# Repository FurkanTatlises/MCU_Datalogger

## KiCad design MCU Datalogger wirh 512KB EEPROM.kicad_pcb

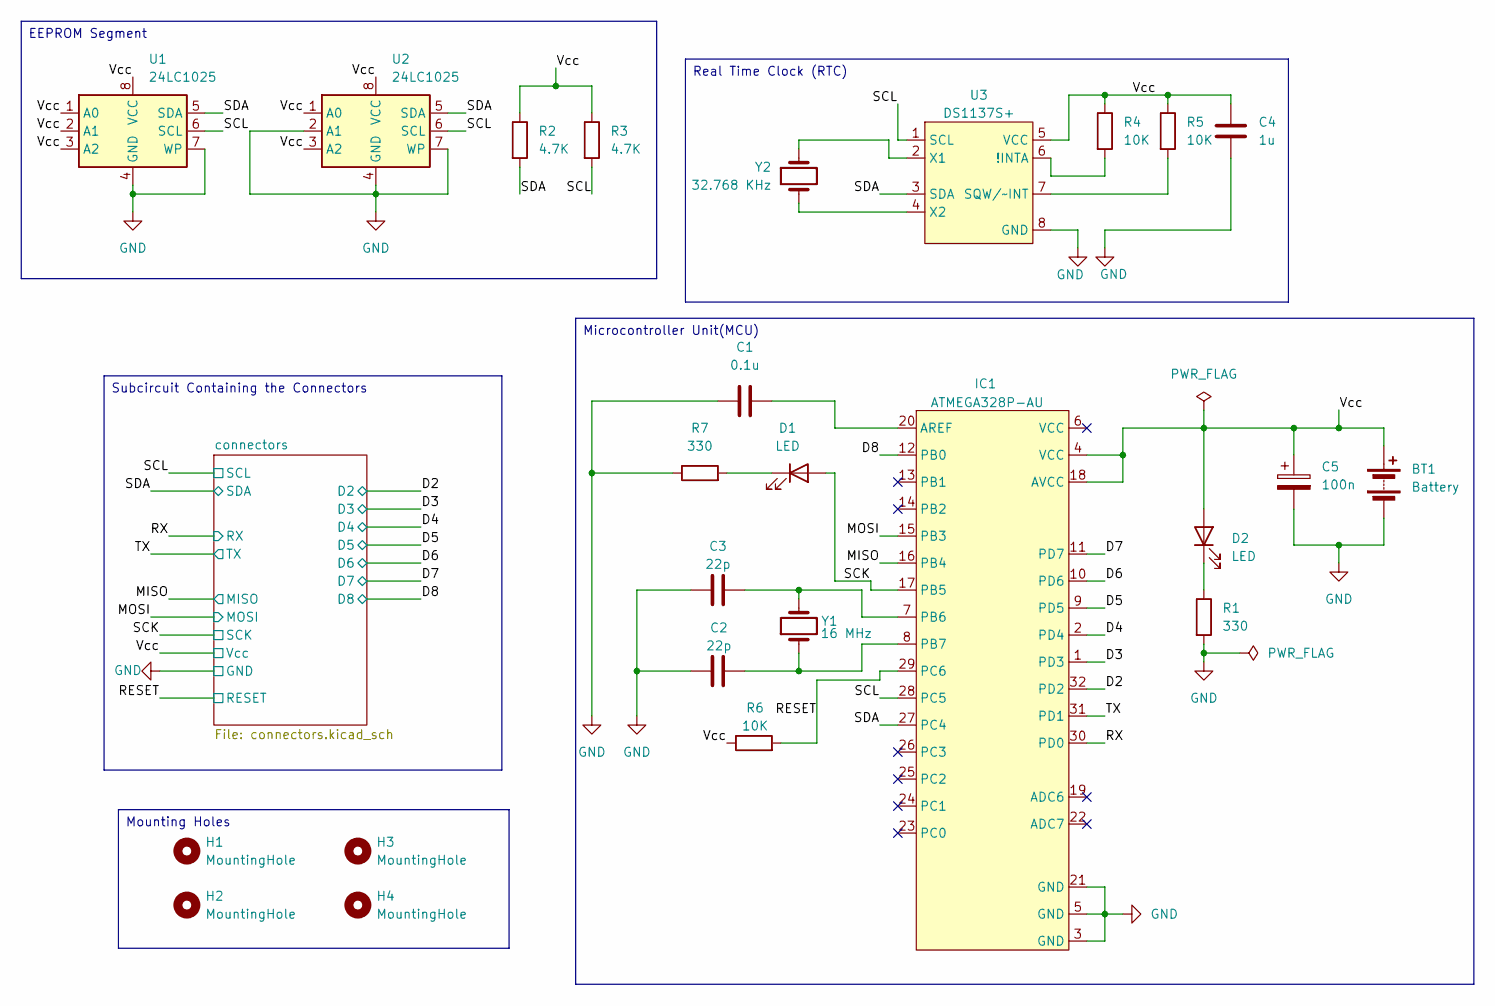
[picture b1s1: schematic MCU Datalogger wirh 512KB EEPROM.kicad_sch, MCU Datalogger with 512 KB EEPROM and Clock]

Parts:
BT1: Battery; PinHeader_1x02_P2.54mm_Vertical
C1: 0.1u; C_1206_3216Metric
C2, C3: 22p; C_1206_3216Metric
C4: 1u; C_1206_3216Metric
C5: 100n; C_1206_3216Metric
D1, D2: LED; LED_1206_3216Metric
H1, H2, H3, H4: MountingHole; MountingHole_2.1mm
IC1: ATMEGA328P-AU
R1, R7: 330; R_0805_2012Metric
R2, R3: 4.7K; R_0805_2012Metric
R4, R5, R6: 10K; R_0805_2012Metric
U1, U2: 24LC1025; SOIC-8_5.3x5.3mm_P1.27mm
U3: DS1137S+; DS1337S+
Y1: 16 MHz; Crystal_SMD_5032-2Pin_5.0x3.2mm
Y2: 32.768 KHz; Crystal_SMD_5032-2Pin_5.0x3.2mm

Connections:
/D2: IC1.32 (PD2); also elsewhere on the board
/D3: IC1.1 (PD3); also elsewhere on the board
/D4: IC1.2 (PD4); also elsewhere on the board
/D5: IC1.9 (PD5); also elsewhere on the board
/D6: IC1.10 (PD6); also elsewhere on the board
/D7: IC1.11 (PD7); also elsewhere on the board
/D8: IC1.12 (PB0); also elsewhere on the board
/MISO: IC1.16 (PB4); also elsewhere on the board
/MOSI: IC1.15 (PB3); also elsewhere on the board
/RESET: IC1.29 (PC6), R6.2; also elsewhere on the board
/RX: IC1.30 (PD0); also elsewhere on the board
/SCK: D1.2 (A), IC1.17 (PB5); also elsewhere on the board
/SCL: IC1.28 (PC5), R3.2, U1.6 (SCL), U2.6 (SCL), U3.1 (SCL); also elsewhere on the board
/SDA: IC1.27 (PC4), R2.2, U1.5 (SDA), U2.5 (SDA), U3.3 (SDA); also elsewhere on the board
/TX: IC1.31 (PD1); also elsewhere on the board
/Vcc: BT1.1 (+), C4.2, C5.1, D2.2 (A), IC1.4 (VCC), IC1.18 (AVCC), R2.1, R3.1, R4.1, R5.1, R6.1, U1.1 (A0), U1.2 (A1), U1.3 (A2), U1.8 (VCC), U2.1 (A0), U2.3 (A2), U2.8 (VCC), U3.5 (VCC); also elsewhere on the board
GND: BT1.2 (-), C1.2, C2.1, C3.1, C4.1, C5.2, IC1.3 (GND), IC1.5 (GND), IC1.21 (GND), R1.2, R7.1, U1.4 (GND), U1.7 (WP), U2.2 (A1), U2.4 (GND), U2.7 (WP), U3.8 (GND); also elsewhere on the board
unnamed: D1.1 (K), R7.2
unnamed: D2.1 (K), R1.1
unnamed: C1.1, IC1.20 (AREF)
unnamed: C3.2, IC1.7 (PB6), Y1.2
unnamed: C2.2, IC1.8 (PB7), Y1.1
unnamed: R4.2, U3.6 (!INTA)
unnamed: R5.2, U3.7 (SQW/~INT)
unnamed: U3.2 (X1), Y2.1
unnamed: U3.4 (X2), Y2.2

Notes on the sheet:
Subcircuit Containing the Connectors
EEPROM Segment
Microcontroller Unit(MCU)
Mounting Holes
Real Time Clock (RTC)

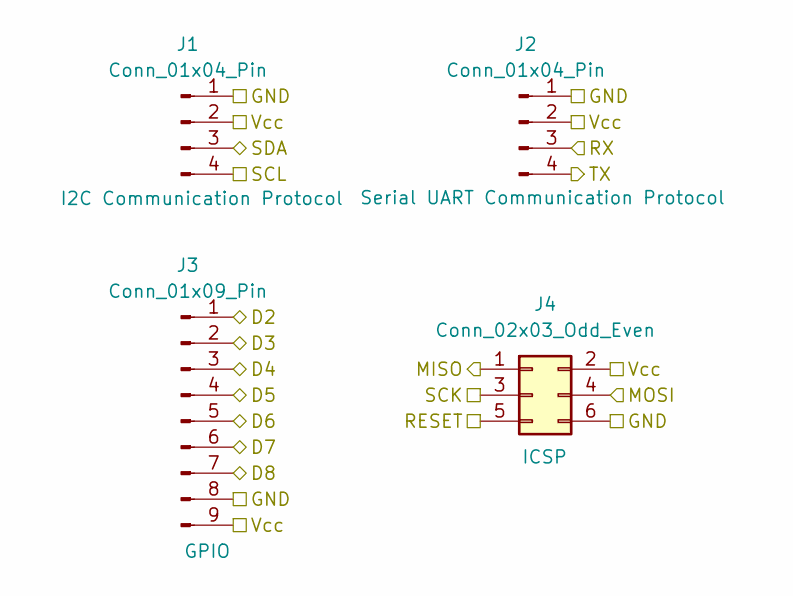
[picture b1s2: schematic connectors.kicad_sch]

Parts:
J1, J2: Conn_01x04_Pin; PinHeader_1x04_P2.54mm_Vertical
J3: Conn_01x09_Pin; PinHeader_1x09_P2.54mm_Vertical
J4: Conn_02x03_Odd_Even; PinHeader_2x03_P2.54mm_Vertical

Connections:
/D2: J3.1; also elsewhere on the board
/D3: J3.2; also elsewhere on the board
/D4: J3.3; also elsewhere on the board
/D5: J3.4; also elsewhere on the board
/D6: J3.5; also elsewhere on the board
/D7: J3.6; also elsewhere on the board
/D8: J3.7; also elsewhere on the board
/MISO: J4.1; also elsewhere on the board
/MOSI: J4.4; also elsewhere on the board
/RESET: J4.5; also elsewhere on the board
/RX: J2.3; also elsewhere on the board
/SCK: J4.3; also elsewhere on the board
/SCL: J1.4; also elsewhere on the board
/SDA: J1.3; also elsewhere on the board
/TX: J2.4; also elsewhere on the board
/Vcc: J1.2, J2.2, J3.9, J4.2; also elsewhere on the board
GND: J1.1, J2.1, J3.8, J4.6; also elsewhere on the board

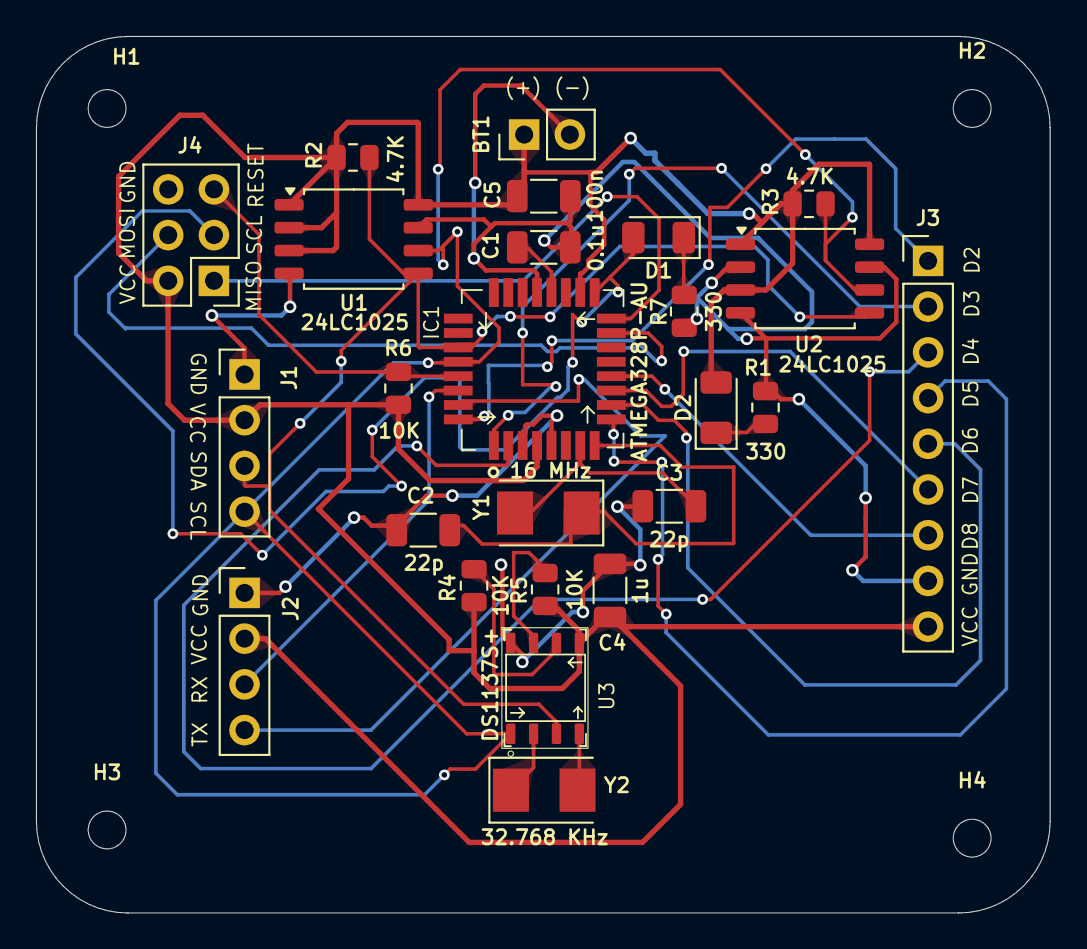
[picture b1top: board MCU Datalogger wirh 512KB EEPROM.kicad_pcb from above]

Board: 2 copper layers, 56.3 x 48.7 mm, 29 parts (0 on the bottom side), 26 nets.

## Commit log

2025-10-22 Set up the schematic diagram in EESchema for the start of the project.
2025-10-25 Added required symbols for the schematic design.
2025-10-25 Arranged the placement of the symbols.
2025-10-25 Assigned values for each component.
2025-10-25 Assigned footprints to the components in EESchema.
2025-10-25 Completed the wiring of the main schematic. Next will be the second schematic that contains the connectors.
2025-10-28 Finished the wiring of the schematic.
2025-11-15 Performed the power net classes to vcc, avcc and gnd connections.
2025-11-15 Done the last ERC and added some comments. The schematic part is done for now.
2025-11-15 Started the 2 layered PCB layout. The components are transfered to layout and proper adjustments are going to be performed later on.
2025-11-15 Done the layout and wiring of the 2 layered PCB.
2025-11-16 While doing the 2 layered PCB layout, I have used a lot of vias. This makes the PCB look a little bit complex. Doing this in 4 layered fashion may enhance the simplicity but the pricing will also inc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
2025-11-16 Added graphics at the back silkscreen and also on the front silkscreen for connector pins.
2025-11-16 Improved some tracks.
2025-11-16 Plotted the gerber and drill files.
2025-11-16 Included values for assembly.
2025-11-16 Done more improvements for the placements in front silkscreen.
2025-11-16 Included the names of ICs to the front silkscreen.
2025-11-16 The 3D model of the ATMEGA microprocessor is not quite right, I will leave it at that since this is only for visualization.
2025-11-19 Created a separate folder for the gerber files on 2 layered version.
2025-11-19 Done the routing of the 4-layer PCB layout.
2025-11-19 Improved the wiring for potential signal interferences.
2025-11-19 Plotted the gerber files for the 4-layer PCB.
2025-11-19 Added a .gitattributes file to prevent override of these 2 separata PCBs.
2025-11-19 Switched to 2 layer to test the structure.
2025-11-19 Tryna test the structure.
2025-11-19 Looks like it is working.
2025-11-22 Fixed the problem with the clock signal. I've added SCK for the clock signal of SPI commmunication protocol.
2025-11-22 Done the wiring of the 4-layered PCB after the clock fixing.
2025-11-22 Done the wiring on the 2-layer pcb after the clock fixing.
2025-11-22 Finished the problem solving.
2025-11-29 Made a small change.
2025-11-29 Included a board characteristic report.
2025-11-29 Addeed a board characteristics report.
2025-12-03 Included teardrops and BOM.
2025-12-03 Included BOM and teardrops.
2025-12-03 Included BOM.
2025-12-03 Merged to changes to the main directory.
2025-12-03 Minor change has happened.
2025-12-03 Included a jobset to print all the overview of the layout and BOM.
2025-12-03 Included JOBSET for plotting the BOM and overview of the layout.
2025-12-03 Included a JOBSET file to plot the overview of the layout and a BOM.
2025-12-03 Made a minor change.
2025-12-07 Done a minor change.
